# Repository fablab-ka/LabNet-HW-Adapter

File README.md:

# LabNet-HW-Adapter
Adapter and translator for rs485, rs232, ttl, pinouts and so on

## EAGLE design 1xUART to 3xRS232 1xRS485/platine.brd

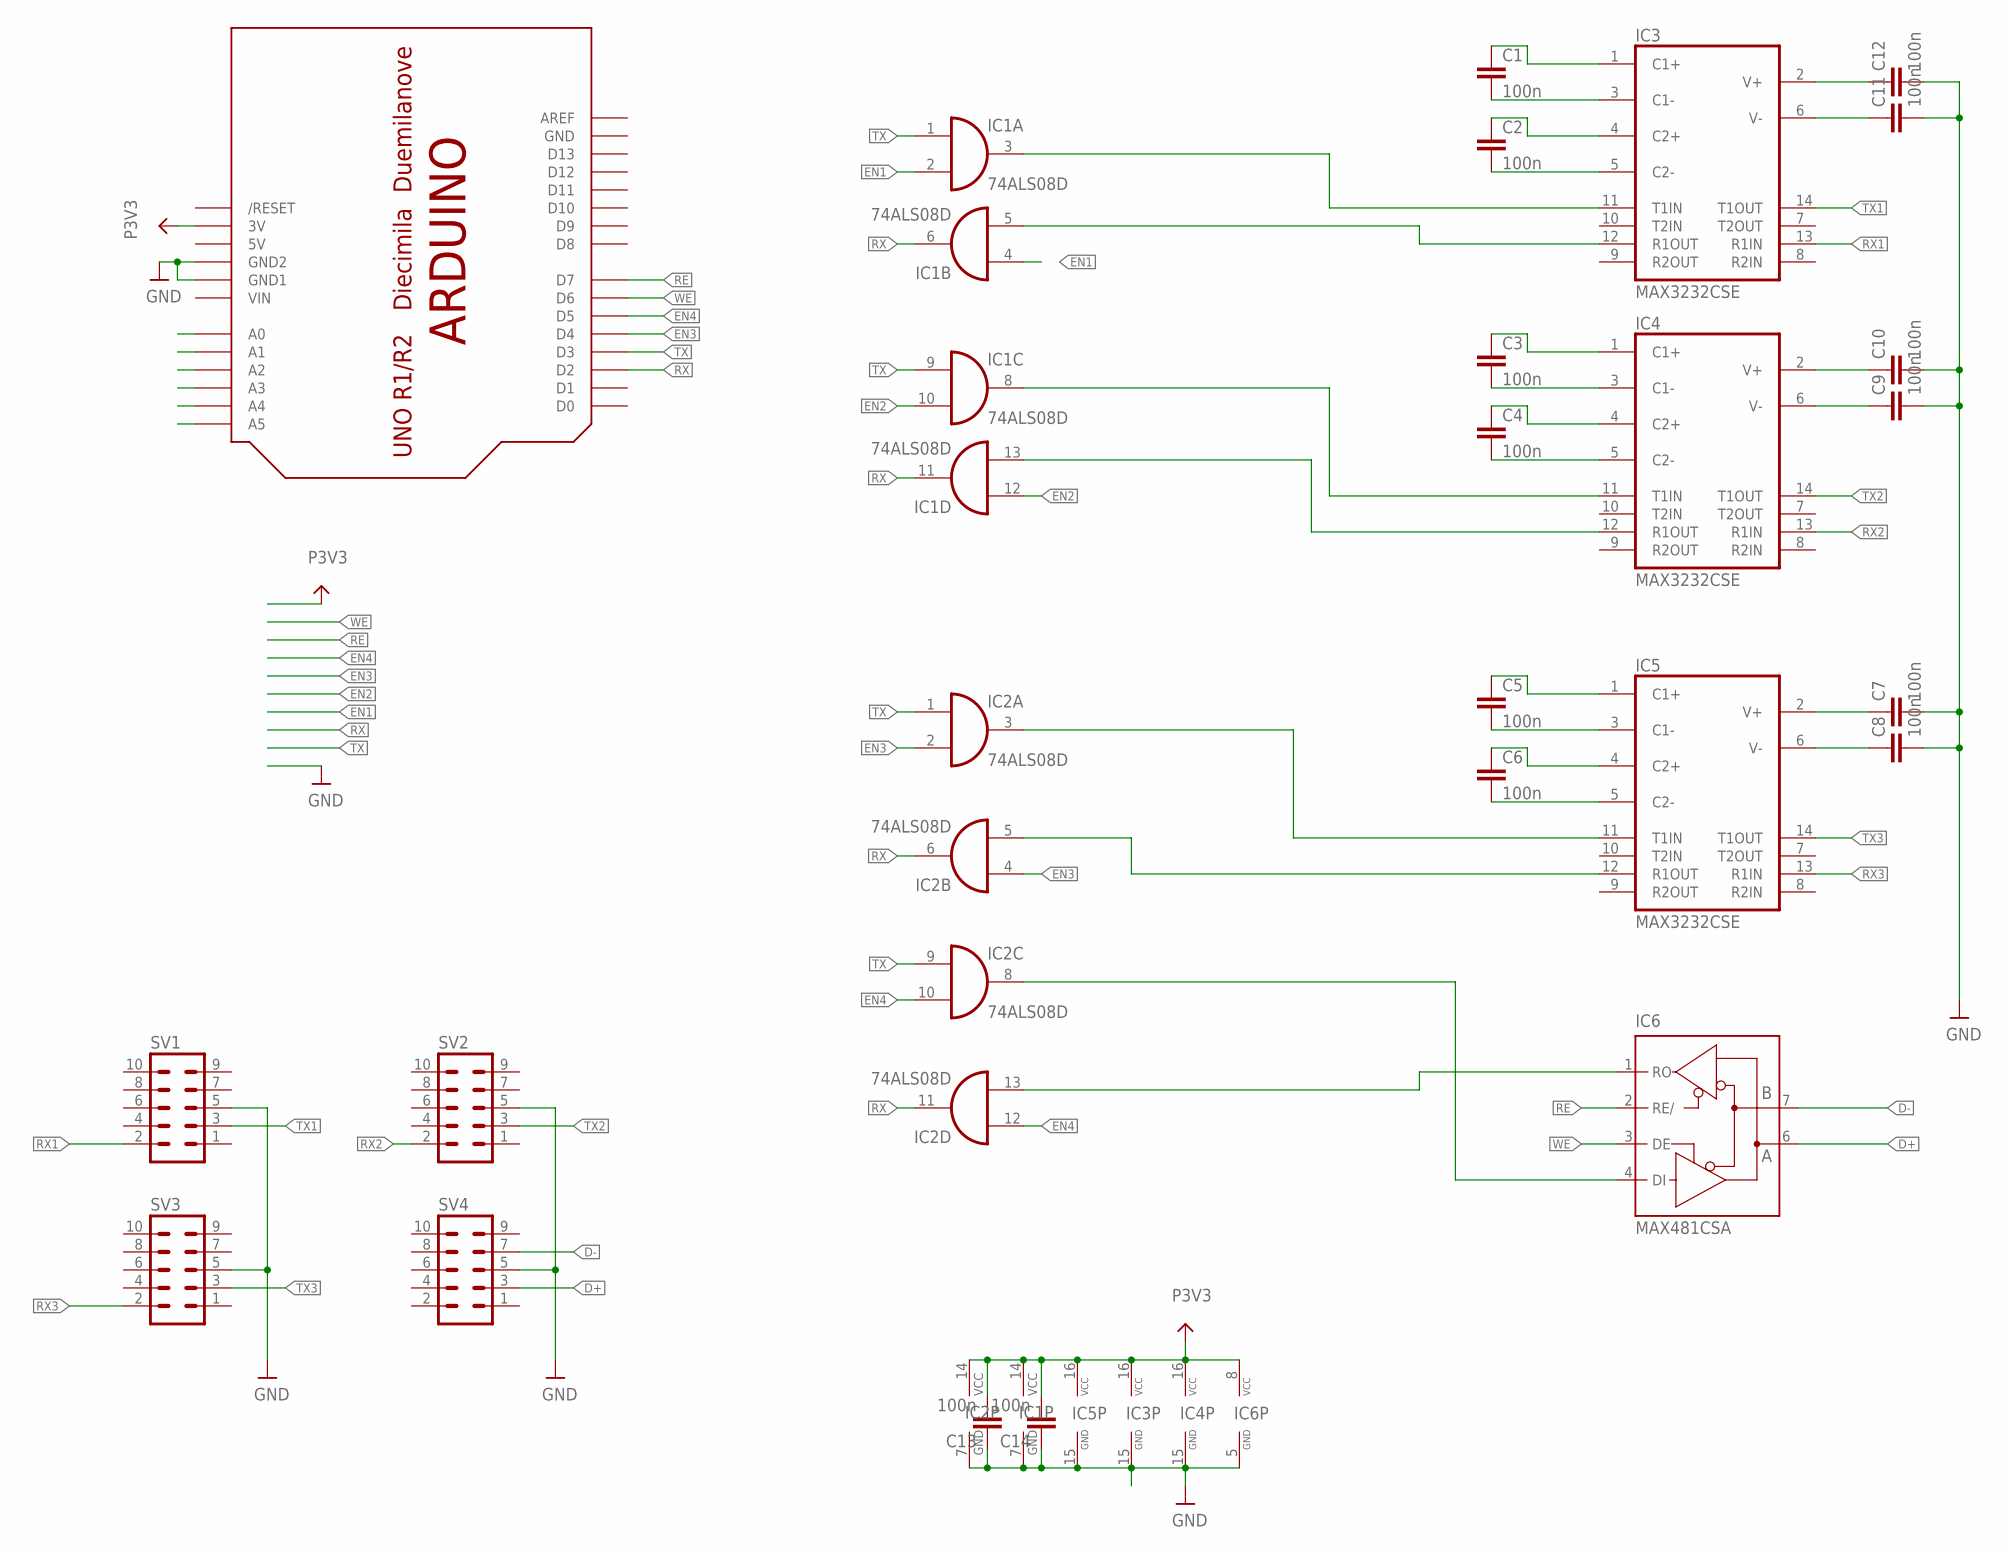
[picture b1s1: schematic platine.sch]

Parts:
C1, C2, C3, C4, C5, C6, C7, C8, C9, C10, C11, C12, C13, C14: 100n; C1210
IC1, IC2: 74ALS08D; SO14
IC3, IC4, IC5: MAX3232CSE; SO16
IC6: MAX481CSA; SO08
SV1, SV2, SV3, SV4: ML10
U$1: ARDUINO-NOHOLE

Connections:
5V: U$1.5V
D+: IC6.6 (A), SV4.3
D-: IC6.7 (B), SV4.7
EN1: IC1.2 (I1), IC1.4 (I0), U$1.A0
EN2: IC1.10 (I1), IC1.12 (I0), U$1.A1
EN3: IC2.2 (I1), IC2.4 (I0), U$1.D4
EN4: IC2.10 (I1), IC2.12 (I0), U$1.D5
GND: C7.2, C8.2, C9.2, C10.2, C11.2, C12.2, C13.1, C14.1, IC1.7 (GND), IC2.7 (GND), IC3.15 (GND), IC4.15 (GND), IC5.15 (GND), IC6.5 (GND), SV1.5, SV2.5, SV3.5, SV4.5, U$1.GND, U$1.GND1, U$1.GND2
unnamed: IC1.5 (I1), IC3.12 (R1OUT)
unnamed: IC1.3 (O), IC3.11 (T1IN)
unnamed: IC1.8 (O), IC4.11 (T1IN)
unnamed: IC1.13 (I1), IC4.12 (R1OUT)
unnamed: IC2.3 (O), IC5.11 (T1IN)
unnamed: IC2.5 (I1), IC5.12 (R1OUT)
unnamed: IC2.8 (O), IC6.4 (DI)
unnamed: IC2.13 (I1), IC6.1 (RO)
unnamed: C6.2, IC5.5 (C2-)
unnamed: C6.1, IC5.4 (C2+)
unnamed: C5.2, IC5.3 (C1-)
unnamed: C5.1, IC5.1 (C1+)
unnamed: C4.2, IC4.5 (C2-)
unnamed: C4.1, IC4.4 (C2+)
unnamed: C3.1, IC4.1 (C1+)
unnamed: C3.2, IC4.3 (C1-)
unnamed: C2.2, IC3.5 (C2-)
unnamed: C2.1, IC3.4 (C2+)
unnamed: C1.2, IC3.3 (C1-)
unnamed: C1.1, IC3.1 (C1+)
unnamed: C12.1, IC3.2 (V+)
unnamed: C11.1, IC3.6 (V-)
unnamed: C7.1, IC5.2 (V+)
unnamed: C8.1, IC5.6 (V-)
unnamed: C10.1, IC4.2 (V+)
unnamed: C9.1, IC4.6 (V-)
P3V3: C13.2, C14.2, IC1.14 (VCC), IC2.14 (VCC), IC3.16 (VCC), IC4.16 (VCC), IC5.16 (VCC), IC6.8 (VCC), U$1.3V
RE: IC6.2 (RE/), U$1.D7
RX: IC1.6 (O), IC1.11 (O), IC2.6 (O), IC2.11 (O), U$1.D2
RX1: IC3.13 (R1IN), SV1.2
RX2: IC4.13 (R1IN), SV2.2
RX3: IC5.13 (R1IN), SV3.2
TX: IC1.1 (I0), IC1.9 (I0), IC2.1 (I0), IC2.9 (I0), U$1.D3
TX1: IC3.14 (T1OUT), SV1.3
TX2: IC4.14 (T1OUT), SV2.3
TX3: IC5.14 (T1OUT), SV3.3
VIN: U$1.VIN
WE: IC6.3 (DE), U$1.D6

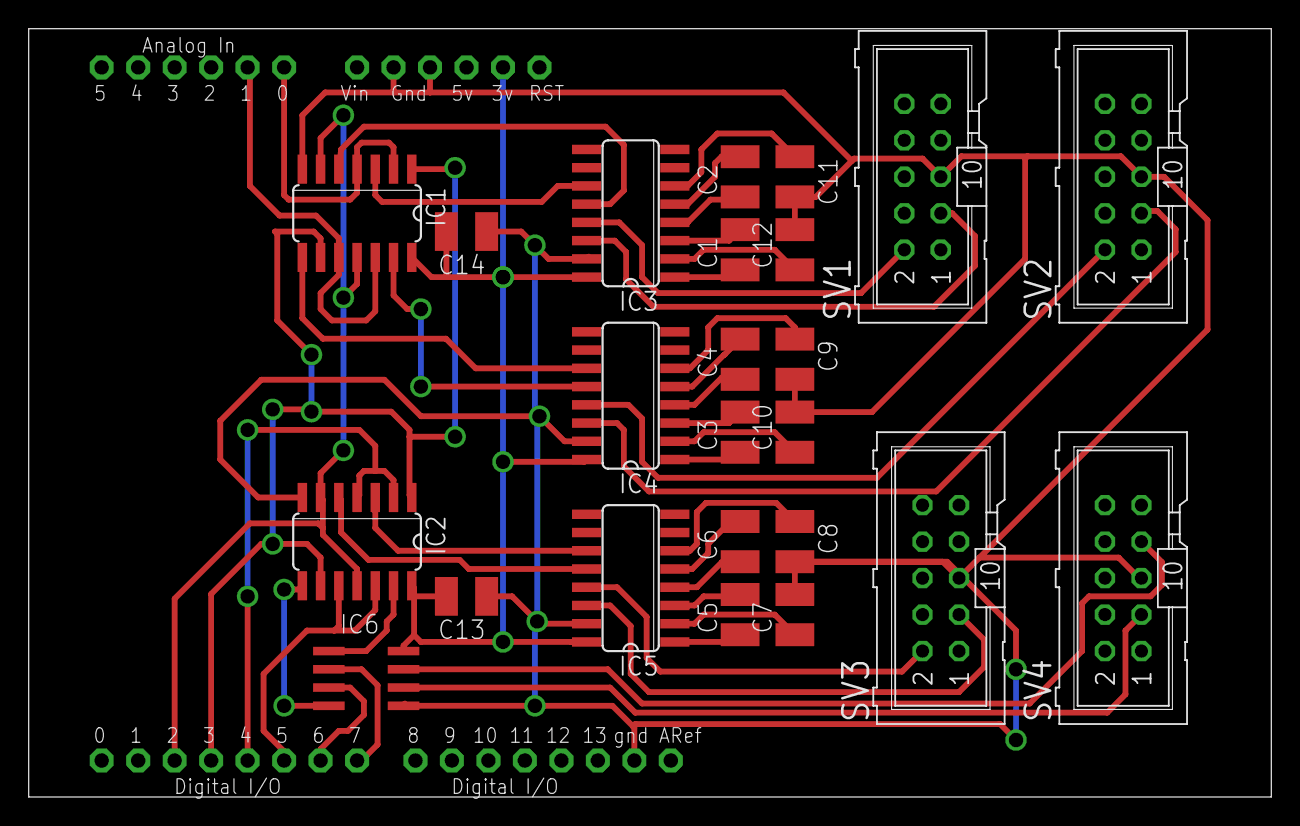
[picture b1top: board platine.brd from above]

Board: 2 copper layers, 86.5 x 53.5 mm, 25 parts (0 on the bottom side), 44 nets.

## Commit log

2015-11-28 redesign for etching
